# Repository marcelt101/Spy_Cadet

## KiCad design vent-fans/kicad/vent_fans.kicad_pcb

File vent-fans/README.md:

# Automatic vent booster fans (v1)

Three quiet 80 mm 5 V fans behind a ~4"-tall supply vent. They run only while
the furnace/AC blower runs. Home Assistant watches your HomeKit thermostat and
switches them through a Pico W on a small carrier PCB. One USB-C phone charger
powers everything.

```
vent-fans/
├── README.md                  ← you are here: design, BOM, install, tuning
├── wiring.md                  ← schematic in ASCII, connector pinouts, field wiring
├── esphome/vent-fans.yaml     ← Pico W firmware (validated with ESPHome 2026.11)
├── homeassistant/automation.yaml
├── sim/                       ← ngspice models, ./run_all.sh, plot.py, results.txt, plots
└── kicad/                     ← KiCad 7 project: schematic, placed board, custom Pico W part
    └── tools/                 ← generators (gen_schematic.py, gen_pcb.py, check_netlist.py)
```

## What changed from the original spec, and why

| # | Original spec | v1 | Why (evidence in `sim/`) |
|---|---|---|---|
| 1 | 100 µF across the fans, no inductor | Add **one 100 µH inductor** between the fans and the MOSFET. That makes a proper low-side buck converter. | A capacitor across a low-side-switched load gets recharged to 5 V on every PWM pulse, so the fans saw nearly full voltage at any setting: **30 % duty still gave 90 % fan current**. With the inductor the fans get smooth DC ≈ duty × 5 V (30 % → 27 %, 60 % → 55 %, ripple ≈ 80 mV). See `plot_speed_vs_duty.png`. |
| 2 | Cap only across the fans | 100 µF + 10 µF **on the 5 V rail** (input) as well | Moving caps alone (no inductor) made it worse: every pulse recharged the fans' internal capacitors through the FET with **13–19 A spikes**. The buck version peaks at **0.4 A**. See `plot_waveforms_60pct.png`. |
| 3 | 25 kHz PWM | 40 kHz | Still inaudible. A 100 µH inductor is enough at this frequency (ripple ≈ 0.15 A). |
| 4 | Speed jumps instantly | **Soft-start in firmware**: 2 % every 20 ms | Going straight from 0 to 60 % rings the LC filter: **2.1 A** inductor peak. With the slew limiter it's **0.44 A**, so a small 1 A inductor never saturates. See `plot_powerup.png`. |
| 5 | IRLZ44N / AO3400 | **AO3400A** (SOT-23) only | Simulated Rds(on) ≈ 32 mΩ at the Pico's 3.3 V gate drive. It dissipates ~6 mW, so no heatsink. The IRLZ44N is only specified from 4 V gate drive and is huge. |
| 6 | Breadboard wiring | **Carrier PCB, 70 × 50 mm**: Pico W socketed, 3 keyed fan headers, optional DS18B20 header | Fewer loose joints in a dusty, warm, vibrating spot. Fans unplug for cleaning. |
| 7 | Automation used `delay` + `trigger.to_state` | `for:` on the triggers, re-sync on HA restart and when the board reconnects | The old version could leave fans running after an HA restart. `for:` doesn't drop a pending off when the thermostat chatters. |
| 8 | ESPHome reboots when HA is down | `reboot_timeout: 0s`, plus optional on-board fallback from a duct probe | The fans keep working (or stay safely off) with HA down. |

What stayed the same: Pico W, 5 V fans, one USB charger, HA in charge, 20 s
start delay, 30 s run-on, fans **off** if anything is unplugged or the Pico is
booting (10 k gate pull-down).

### Simulation summary (`sim/results.txt`, 3 × fans, 5.1 V charger + 1 m cable)

| Circuit | duty → fan current (% of full) | FET peak (60 %) | 5 V rail min (30 %) |
|---|---|---|---|
| Original spec | 30→90, 60→97, 80→99 | 0.78 A | 4.40 V |
| Caps on rail, no L | 30→76, 60→90, 80→97 | **13.4 A** | 4.52 V |
| **v1 buck** | **30→27, 60→55, 80→78** | **0.40 A** | 5.05 V |

The models are approximations: the AO3400A is a VDMOS fit to its datasheet, and
each fan is modelled as a reverse diode + 1 µF + 33 Ω + 1 mH. The comparison
between circuits is what matters, not the third digit. To re-run:
`cd sim && ./run_all.sh && python3 plot.py` (needs ngspice, numpy and matplotlib).

## Bill of materials

| Ref | Qty | Part | Footprint | Notes |
|---|---|---|---|---|
| U1 | 1 | Raspberry Pi Pico W, plus 2× 20-pin female headers | 2×20 THT | Socketed, so it can be swapped or reflashed |
| Q1 | 1 | AO3400A N-MOSFET | SOT-23 | Logic-level, 30 V, 5.7 A |
| L1 | 1 | 100 µH shielded power inductor, **Isat ≥ 1 A, DCR ≤ 0.4 Ω** | Bourns SRR1260 (12.5 mm) | e.g. SRR1260-101M. Check Isat on the datasheet of whatever you buy. |
| D1 | 1 | SS14 Schottky, 1 A 40 V (SMD 1N5819) | SMA | Stripe (cathode) to +5 V |
| C1, C3 | 2 | 100 µF 10 V+ low-ESR electrolytic | radial 6.3 mm, 2.5 mm pitch | C1 = input, C3 = across the fans |
| C2 | 1 | 10 µF 16 V X7R ceramic | 1206 | Close to Q1/D1 |
| R1 | 1 | 100 Ω | 0805 | gate series resistor |
| R2 | 1 | 10 kΩ | 0805 | gate pull-down |
| J1–J3 | 3 | 3-pin 2.54 mm fan header (KF2510 / Molex KK style) | `FanPinHeader_1x03` | 2-pin fan plugs fit pins 1–2 |
| J4, R3 | 1 + 1 | 3-pin header + 4.7 kΩ 0805 | | **Optional**, only with the DS18B20 probe |
| — | 3 | 80 mm **5 V** fans, 15 or 25 mm thick, sleeve/hydraulic bearing, ≤ 0.25 A | | Pick the lowest-RPM/dBA listing. Budget generic is fine. |
| — | 1 | USB-C charger (5 V, ≥ 1.5 A) + USB-C → micro-USB cable | | Plugs into the Pico's own USB port |
| — | 1 | Waterproof DS18B20 probe | | Optional |

Total draw ≈ 0.5 A at full speed, ~0.25 A at the default setting.

## Build

1. **PCB**: open `kicad/vent_fans.kicad_pro` in KiCad 7 or later. The
   schematic is complete and the board is placed with nets assigned. You do the
   routing; see [Routing the board](#routing-the-board).
2. **Solder** SMD parts first, then the caps, headers and Pico sockets.
   Check the polarity of C1/C3 (+) and D1 (stripe toward the +5V side).
3. **Firmware**: in the ESPHome add-on on your Proxmox HA, create a new device,
   paste `esphome/vent-fans.yaml`, add the secrets (`esphome/secrets.example.yaml`
   shows the names), plug the Pico W into your PC by USB and install. After that,
   updates go over Wi-Fi.
4. **Bench test** before it goes in the wall. Plug in the charger with the fans
   attached. In HA, turn on `fan.vent_fans`: the fans should ramp up over about
   a second. Measure across a fan connector (pin 2 to pin 1): ≈ 2.7 V at 1 %,
   ≈ 4 V at 60 %, ≈ 4.9 V at 100 %.
5. **Automation**: in HA, go to Developer Tools → States, filter `climate.`, and
   find your thermostat. Check that it has an `hvac_action` attribute that
   changes between `idle` and `heating`/`cooling`. HomeKit Controller thermostats
   normally do. Paste `homeassistant/automation.yaml` into a new automation and
   replace `climate.thermostat` (3 places).

## Routing the board

The board in `kicad/vent_fans.kicad_pcb` is 70 × 50 mm and two-layer. It already
has a GND pour on both layers and a copper keep-out under the Pico W antenna.
The `Power` net class (0.8 mm tracks) covers +5V, GND, FAN- and SW. Signals
default to 0.3 mm.

1. Open the PCB and press **B** to refill zones. The ratsnest shows the 20
   connections still to route.
2. Route the **switching loop** first and keep it tiny: C2 → D1 cathode, D1
   anode → Q1 drain, Q1 source → GND via next to C2's GND pad. This is the only
   fast-edge loop on the board.
3. SW (Q1 drain / D1 anode / L1 pin 2) is the noisy node. Keep it short and
   on the top layer, with no long runs.
4. +5V: from Pico pin 40 (top-left corner pad) to C1 and C2, then on to the fan
   headers' pin 2 and C3+. Use 0.8 mm or wider.
5. FAN-: from L1 pin 1 to C3−, then to pin 1 of J1–J3.
6. GP15 (bottom-right Pico pad) → R1 → gate. R2 goes from gate to GND.
7. Optional: GP16 → J4 pin 2 → R3 → 3V3 (Pico pin 36).
8. Stitch the two GND pours with a few vias, keeping them away from the
   antenna keep-out. Run **Inspect → Design Rules Checker** until it's clean.
9. **File → Fabrication Outputs → Gerbers + Drill**, zip them and order (any
   2-layer, 1.6 mm, HASL service).

`kicad/tools/` regenerates everything from one parts table, if you want to change
a part:
`python3 tools/gen_schematic.py && python3 tools/check_netlist.py && /usr/bin/python3 tools/gen_pcb.py`.
Note that this overwrites any routing you've done, so only use it before you route.

## Tuning

- **Speed**: `speed: 60` in the automation. With smooth DC the fans are much
  quieter at a given speed than with chopped PWM. Try 30–60 %.
- **Fans won't start at low speed**: raise `min_power` (0.55 ≈ 2.7 V) in
  `vent-fans.yaml`.
- **Delays**: the `for:` values in the automation (20 s on, 30 s run-on).
- **Your thermostat only shows `idle`/`heating`** (no `cooling`, or the
  attribute is missing): use the DS18B20 option. Its on-board fallback logic is
  in the YAML, or you can make the HA automation trigger on `sensor.duct_temperature`.

## Safety and install notes

- **FAN- is not ground.** The fans' black wires sit at about 5 V minus the fan
  voltage. Never tie a fan's black wire to GND, the metal duct or the Pico.
- Keep the PCB and charger outside the duct, in the wall cavity or a small box
  next to the boot. Only the fan leads (and the probe) go into the airstream. Use
  plenum-rated cable if your local code requires it for runs inside the duct.
- Keep fans away from electric heat strips. With a heat pump or electric
  furnace, mount the fans at the register end only.
- Mount fans on foam or rubber grommets, seal the frame with foam
  weatherstrip, and have the fans blow into the room.
- If Wi-Fi or HA is down, the fans stay off (or run from the duct probe if it's
  fitted). A Pico crash or unplugged charger also means fans off.

## Still open

- **Vent width and depth**: needed for the optional 3D-printed fan frame
  (`frame.scad`).
- **Thermostat model**: to confirm it exposes `hvac_action` through HomeKit.

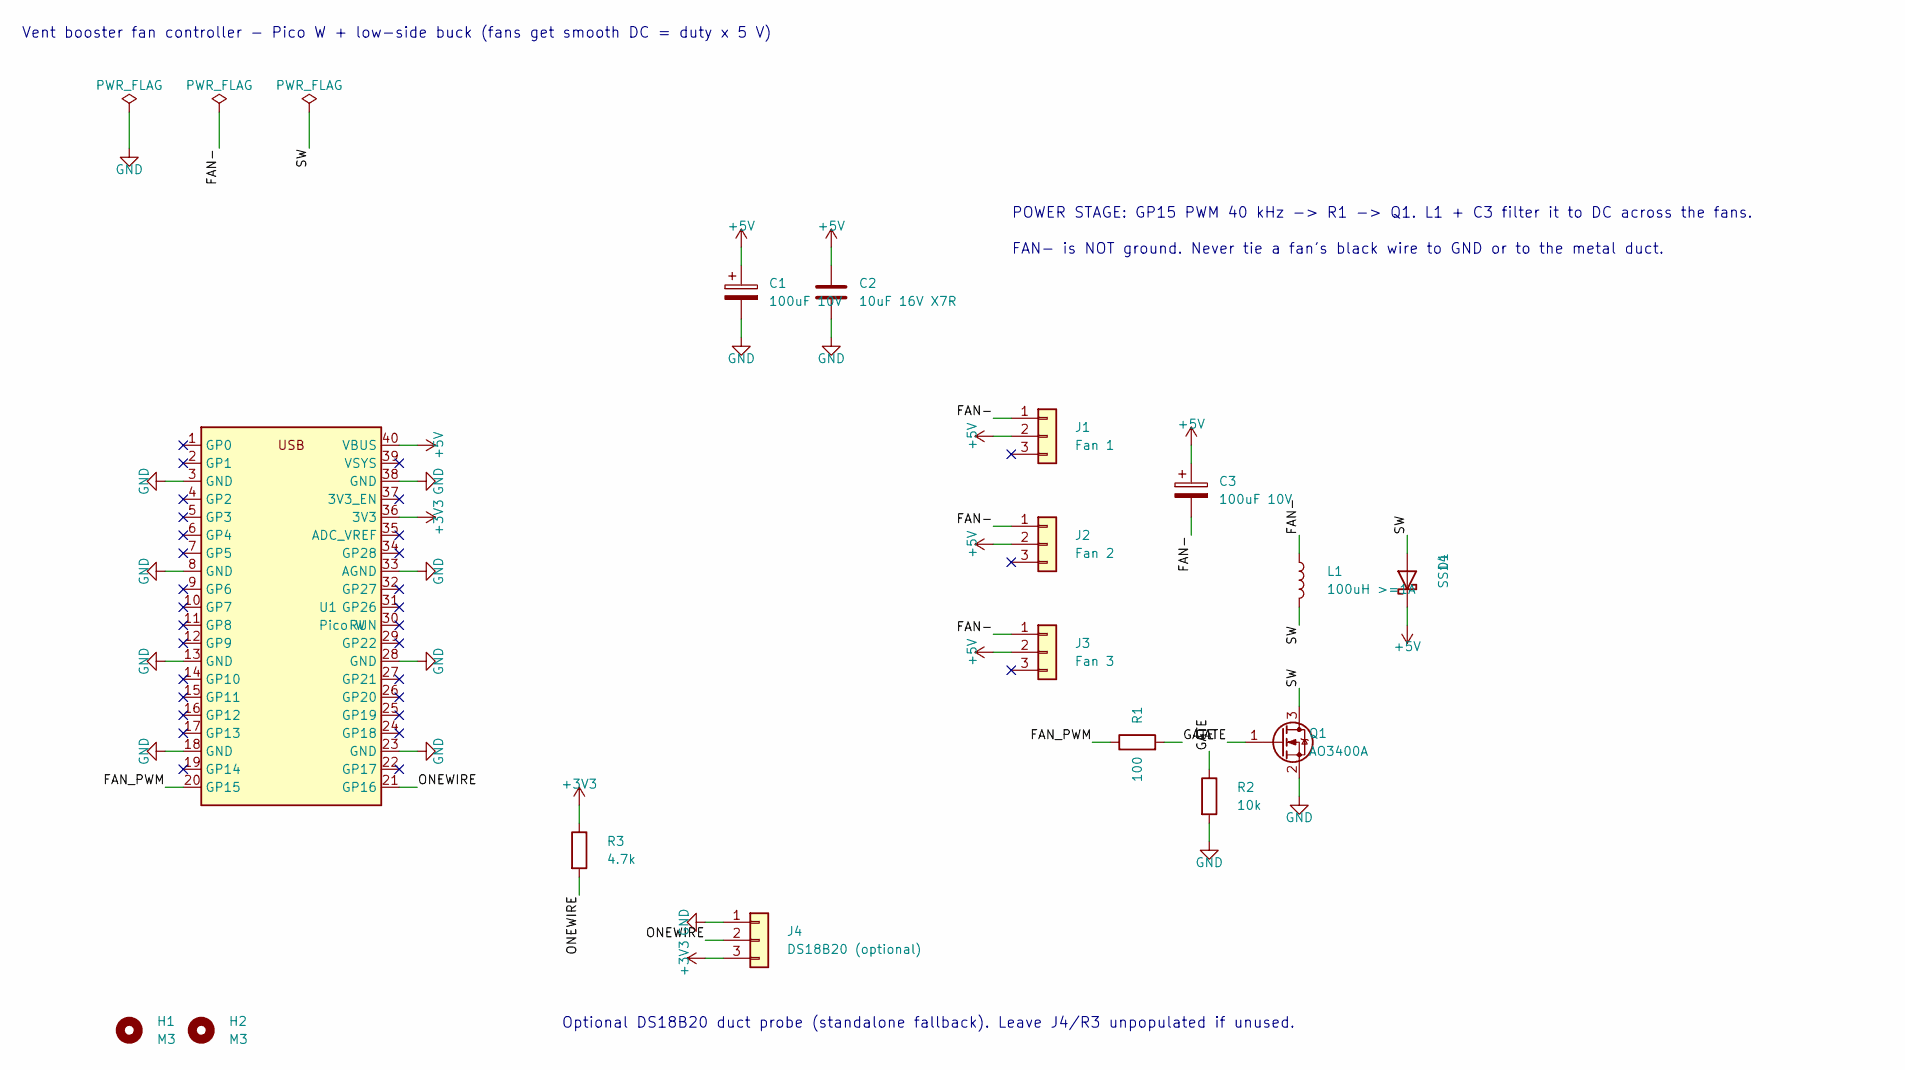
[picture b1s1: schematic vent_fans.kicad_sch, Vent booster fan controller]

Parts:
C1, C3: 100uF 10V; CP_Radial_D6.3mm_P2.50mm
C2: 10uF 16V X7R; C_1206_3216Metric
D1: SS14; D_SMA
H1, H2: M3; MountingHole_3.2mm_M3
J1: Fan 1; FanPinHeader_1x03_P2.54mm_Vertical
J2: Fan 2; FanPinHeader_1x03_P2.54mm_Vertical
J3: Fan 3; FanPinHeader_1x03_P2.54mm_Vertical
J4: DS18B20 (optional); PinHeader_1x03_P2.54mm_Vertical
L1: 100uH >=1A; L_Bourns_SRR1260
Q1: AO3400A; SOT-23
R1: 100; R_0805_2012Metric
R2: 10k; R_0805_2012Metric
R3: 4.7k; R_0805_2012Metric
U1: Pico W; RaspberryPi_PicoW_THT

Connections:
+3V3: J4.3, R3.1, U1.36 (3V3)
+5V: C1.1, C2.1, C3.1, D1.1 (K), J1.2, J2.2, J3.2, U1.40 (VBUS)
FAN-: C3.2, J1.1, J2.1, J3.1, L1.1
FAN_PWM: R1.1, U1.20 (GP15)
GATE: Q1.1 (G), R1.2, R2.1
GND: C1.2, C2.2, J4.1, Q1.2 (S), R2.2, U1.3 (GND), U1.8 (GND), U1.13 (GND), U1.18 (GND), U1.23 (GND), U1.28 (GND), U1.33 (AGND), U1.38 (GND)
ONEWIRE: J4.2, R3.2, U1.21 (GP16)
SW: D1.2 (A), L1.2, Q1.3 (D)

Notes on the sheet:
Vent booster fan controller - Pico W + low-side buck (fans get smooth DC = duty x 5 V)
POWER STAGE: GP15 PWM 40 kHz -> R1 -> Q1. L1 + C3 filter it to DC across the fans.
FAN- is NOT ground. Never tie a fan's black wire to GND or to the metal duct.
Optional DS18B20 duct probe (standalone fallback). Leave J4/R3 unpopulated if unused.

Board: 2 copper layers, 16 parts (0 on the bottom side), 8 nets, no tracks yet.
